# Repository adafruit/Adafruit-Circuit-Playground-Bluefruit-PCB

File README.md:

## Adafruit Adafruit Circuit Playground Bluefruit PCB

<a href="http://www.adafruit.com/products/4333"><br/>
Click here to purchase one from the Adafruit shop</a>

PCB files for the Adafruit Adafruit Circuit Playground Bluefruit. 

Format is EagleCAD schematic and board layout
* https://www.adafruit.com/product/4333

### Description

Circuit Playground Bluefruit is our third board in the Circuit Playground series, another step towards a perfect introduction to electronics and programming. We've taken the popular Circuit Playground Express and made it even better! Now the main chip is an nRF52840 microcontroller which is not only more powerful, but also comes with Bluetooth Low Energy support for wireless connectivity.

The board is round and has alligator-clip pads around it so you don't have to solder or sew to make it work. You can power it from USB, a AAA battery pack, or with a Lipoly battery (for advanced users). Circuit Playground Bluefruit has built-in USB support. Built in USB means you plug it in to program it and it just shows up, no special cable or adapter required. Just program your code into the board then take it on the go!

Here's some of the great goodies baked in to each Circuit Playground Bluefruit:

* 1 x nRF52840 Cortex M4 processor with Bluetooth Low Energy support
* 10 x mini NeoPixels, each one can display any color
* 1 x Motion sensor (LIS3DH triple-axis accelerometer with tap detection, free-fall detection)
* 1 x Temperature sensor (thermistor)
* 1 x Light sensor (phototransistor). Can also act as a color sensor and pulse sensor.
* 1 x Sound sensor (MEMS microphone)
* 1 x Mini speaker with class D amplifier (7.5mm magnetic speaker/buzzer)
* 2 x Push buttons, labeled A and B
* 1 x Slide switch
* 8 x alligator-clip friendly input/output pins
* Includes I2C, UART, 6 pins that can do analog inputs, multiple PWM outputs
* Green "ON" LED so you know its powered
* Red "#13" LED for basic blinking
* Reset button
* 2 MB of SPI Flash storage, used primarily with CircuitPython to store code and libraries.
* MicroUSB port for programming and debugging
* USB port can act like serial port, keyboard, mouse, joystick or MIDI!

### License

Adafruit invests time and resources providing this open source design, please support Adafruit and open-source hardware by purchasing products from [Adafruit](https://www.adafruit.com)!

Designed by Limor Fried/Ladyada for Adafruit Industries.

Creative Commons Attribution/Share-Alike, all text above must be included in any redistribution. 
See license.txt for additional details.

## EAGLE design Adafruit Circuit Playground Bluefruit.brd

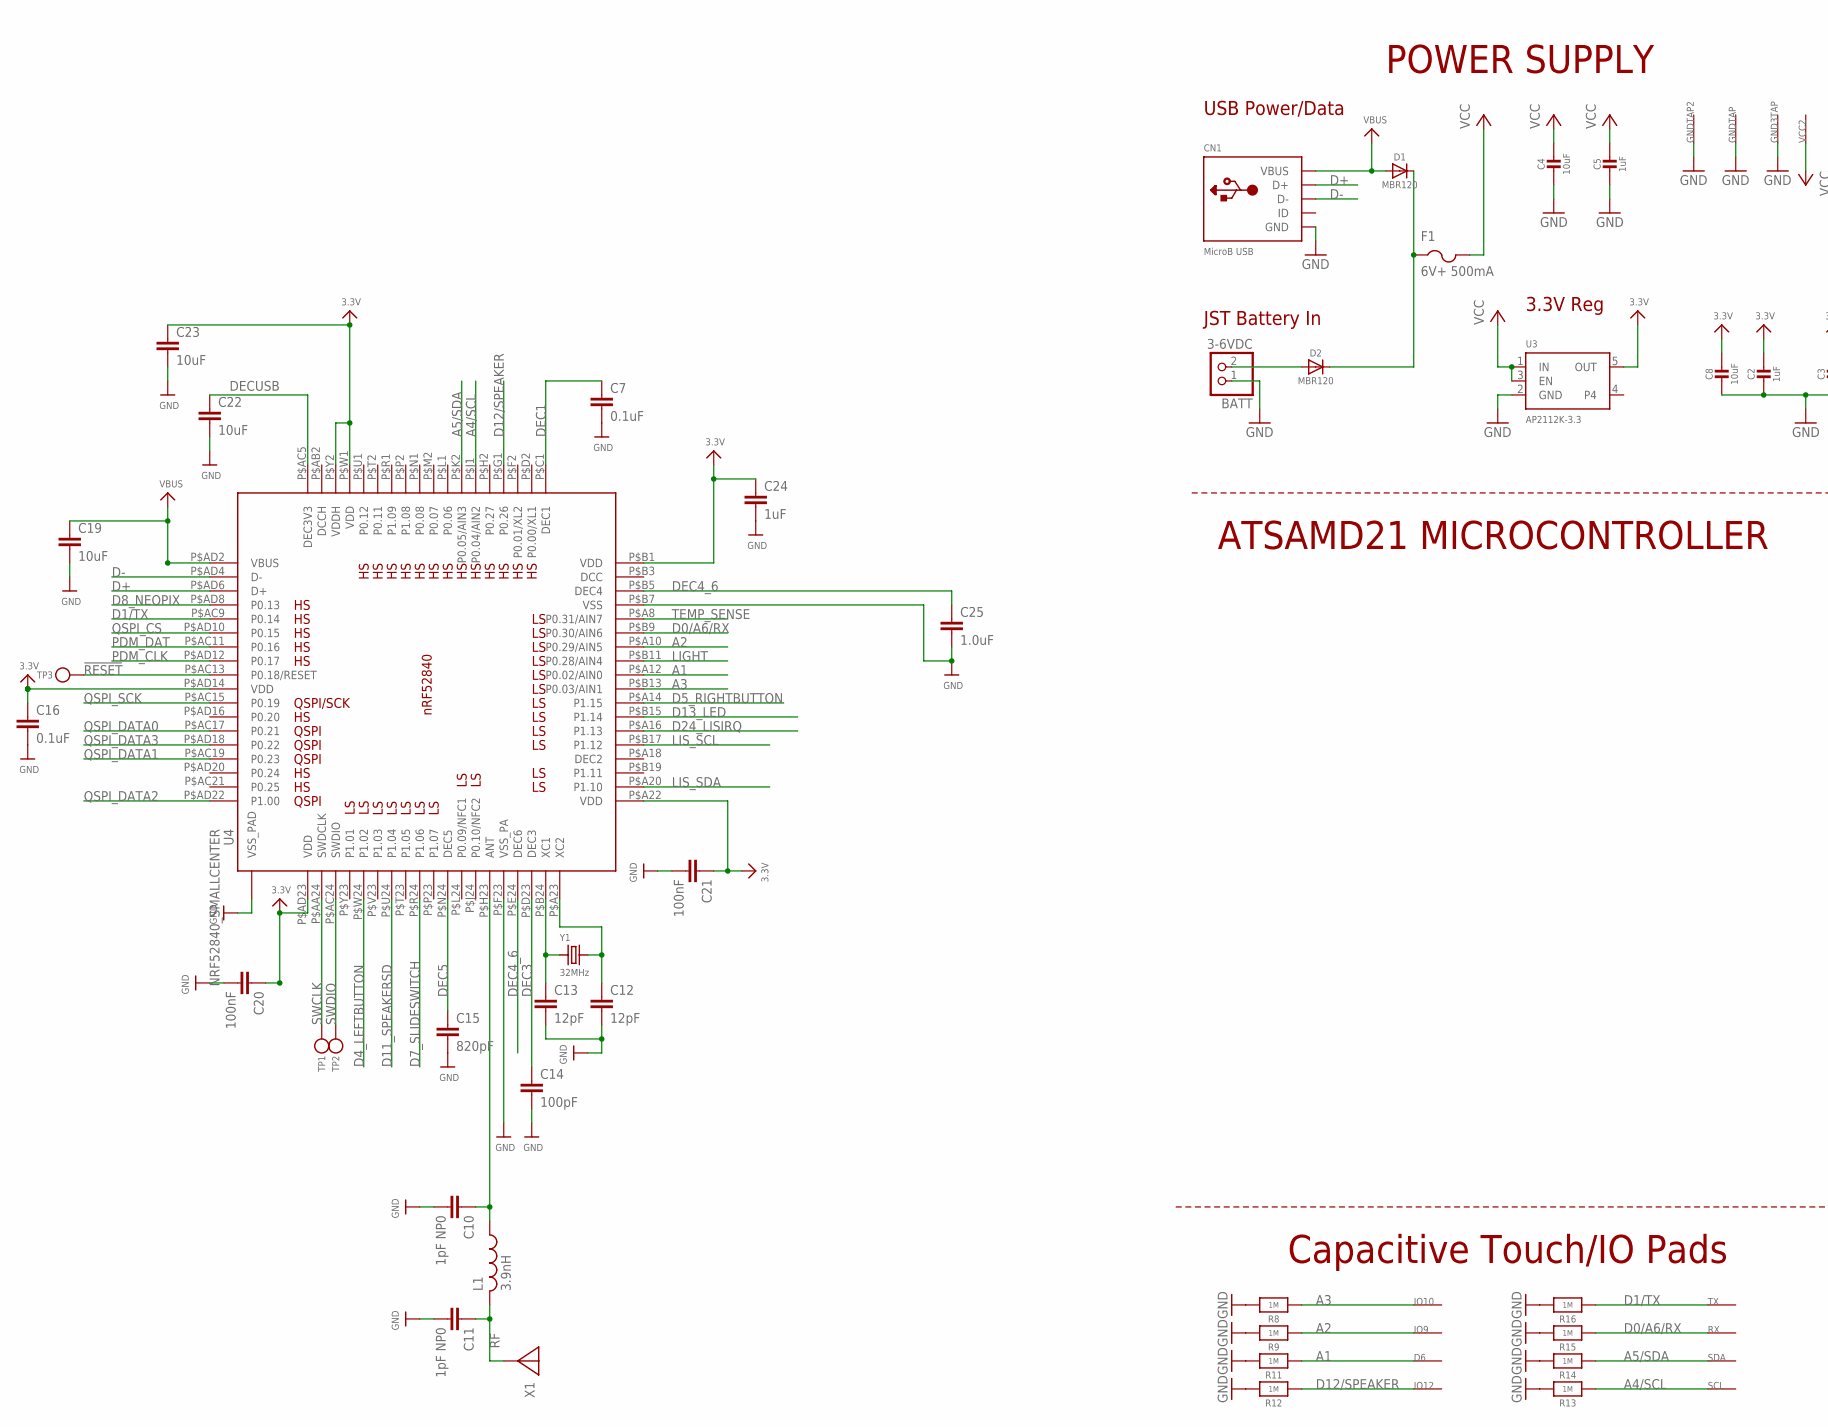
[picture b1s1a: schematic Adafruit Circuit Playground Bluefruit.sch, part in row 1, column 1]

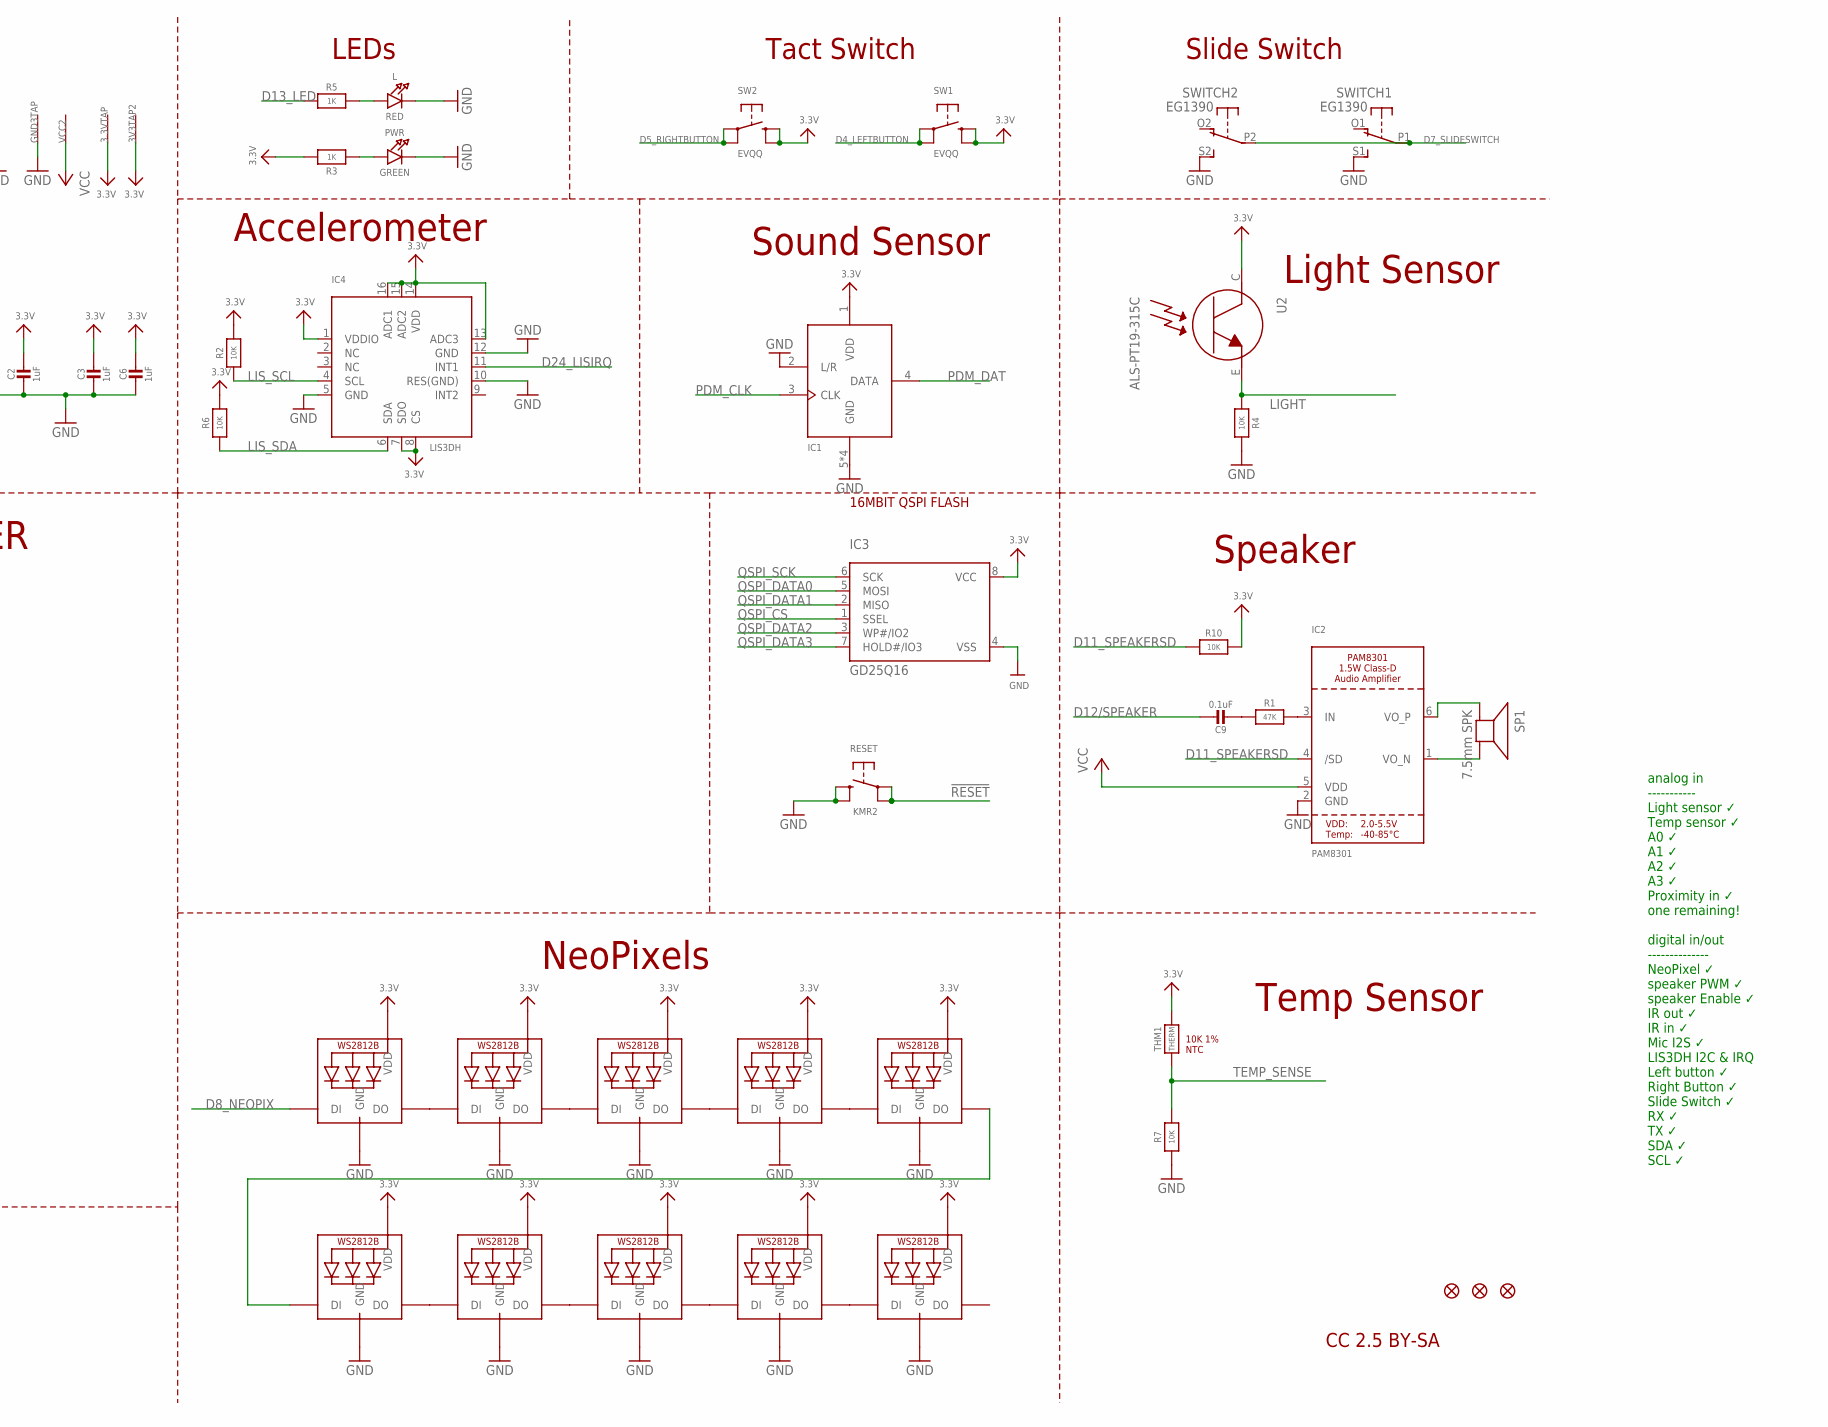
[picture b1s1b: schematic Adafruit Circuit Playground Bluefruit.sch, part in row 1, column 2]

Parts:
3.3VTAP, 3V3TAP2: SEWTAP-ALLIGATOR; SEWALLI
BATT: 3-6VDC; JSTPH2
C2, C3, C5, C6: 1uF; 0603-NO
C4, C8: 10uF; 0805-NO
C7: 0.1uF; RESC0603_N
C9: 0.1uF; 0603-NO
C10, C11: 1pF NP0; RESC0402_N
C12, C13: 12pF; RESC0402_N
C14: 100pF; RESC0402_N
C15: 820pF; RESC0402_N
C16: 0.1uF; RESC0402_N
C19, C22, C23: 10uF; RESC0805_N
C20, C21: 100nF; RESC0402_N
C24: 1uF; RESC0603_N
C25: 1.0uF; RESC0603_N
CN1: MicroB USB; 4UCONN_20329_V2
D1, D2: MBR120; SOD-123
D6: SEWTAP-ALLIGATOR; SEWALLI
F1: 6V+ 500mA; R1206
GND3TAP: SEWTAP-ALLIGATOR; SEWALLI
GNDTAP, GNDTAP2: SEWTAP-ALLIGATOR; SEWALLI
IC1: MIC_PDM; SPK0415HM4H
IC2: PAM8301; SOT23-6
IC3: GD25Q16; USON8
IC4: LIS3DH; LGA16_3X3MM
IO9, IO10, IO12: SEWTAP-ALLIGATOR; SEWALLI
L: RED; CHIPLED_0805_NOOUTLINE
L1: 3.9nH; RESC0402_N
LED1, LED2, LED3, LED4, LED5, LED6, LED7, LED8, LED9, LED10: WS2812B3535; LED3535
PWR: GREEN; CHIPLED_0805_NOOUTLINE
R1: 47K; 0603-NO
R2, R4, R6, R7, R10: 10K; 0603-NO
R3, R5: 1K; 0603-NO
R8, R9, R11, R12, R13, R14, R15, R16: 1M; 0603-NO
RESET: KMR2; BTN_KMR2_4.6X2.8
RX: SEWTAP-ALLIGATOR; SEWALLI
SCL: SEWTAP-ALLIGATOR; SEWALLI
SDA: SEWTAP-ALLIGATOR; SEWALLI
SP1: 7.5mm SPK; BUZZER_SMT_7.5MM
SW1, SW2: EVQQ; EVQ-Q2_SMALLER
SWITCH: EG1390
THM1: THERM; _0402
TP1, TP2, TP3: TESTPOINTROUND1.5MMNO; TESTPOINT_ROUND_1.5MM_NO
TX: SEWTAP-ALLIGATOR; SEWALLI
U2: ALS-PT19-315C
U3: AP2112K-3.3; SOT23-5
U4: NRF52840_SMALLCENTER; AQFN50P700X800X85_HS-74N_SMALLCENTER
U$2, U$3, U$6: FIDUCIAL_1MM
VCC2: SEWTAP-ALLIGATOR; SEWALLI
X1: ANTENNA_JOHANSON_2450AT18B100; ANT_2450AT18B100
Y1: 32MHz; CRYSTAL_2.5X2

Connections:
3.3V: 3.3VTAP.P$1, 3V3TAP2.P$1, C2.1, C3.1, C6.1, C8.1, C16.1, C20.1, C21.1, C23.1, C24.1, IC1.1 (VDD), IC3.8 (VCC), IC4.1 (VDDIO), IC4.7 (SDO), IC4.8 (CS), IC4.13 (ADC3), IC4.14 (VDD), IC4.15 (ADC2), IC4.16 (ADC1), LED1.2 (VDD), LED2.2 (VDD), LED3.2 (VDD), LED4.2 (VDD), LED5.2 (VDD), LED6.2 (VDD), LED7.2 (VDD), LED8.2 (VDD), LED9.2 (VDD), LED10.2 (VDD), R2.2, R3.2, R6.2, R10.2, SW1.B (S), SW1.B' (S1), SW2.B (S), SW2.B' (S1), THM1.2, U2.C, U3.5 (OUT), U4.P$A22 (VDD), U4.P$AD14 (VDD), U4.P$AD23 (VDD), U4.P$B1 (VDD), U4.P$W1 (VDD), U4.P$Y2 (VDDH)
!RESET: RESET.A, RESET.A' (P1), TP3.P$1, U4.P$AC13 (P0.18/RESET)
A1: D6.P$1, R11.1, U4.P$A12 (P0.02/AIN0)
A2: IO9.P$1, R9.1, U4.P$A10 (P0.29/AIN5)
A3: IO10.P$1, R8.1, U4.P$B13 (P0.03/AIN1)
A4/SCL: R13.1, SCL.P$1, U4.P$J1 (P0.04/AIN2)
A5/SDA: R14.1, SDA.P$1, U4.P$K2 (P0.05/AIN3)
D0/A6/RX: R15.1, RX.P$1, U4.P$B9 (P0.30/AIN6)
D1/TX: R16.1, TX.P$1, U4.P$AC9 (P0.14)
D4_LEFTBUTTON: SW1.A, SW1.A' (P1), U4.P$W24 (P1.02)
D5_RIGHTBUTTON: SW2.A, SW2.A' (P1), U4.P$A14 (P1.15)
D7_SLIDESWITCH: SWITCH.P1, SWITCH.P2, U4.P$R24 (P1.06)
D8_NEOPIX: LED6.1 (DI), U4.P$AD8 (P0.13)
D11_SPEAKERSD: IC2.4 (/SD), R10.1, U4.P$U24 (P1.04)
D12/SPEAKER: C9.1, IO12.P$1, R12.1, U4.P$G1 (P0.26)
D13_LED: R5.1, U4.P$B15 (P1.14)
D24_LISIRQ: IC4.11 (INT1), U4.P$A16 (P1.13)
D+: CN1.D+, U4.P$AD6 (D+)
D-: CN1.D-, U4.P$AD4 (D-)
DEC1: C7.1, U4.P$C1 (DEC1)
DEC3: C14.1, U4.P$D23 (DEC3)
DEC4_6: C25.1, U4.P$B5 (DEC4), U4.P$E24 (DEC6)
DEC5: C15.1, U4.P$N24 (DEC5)
DECUSB: C22.1, U4.P$AC5 (DEC3V3)
GND: BATT.1, C2.2, C3.2, C4.2, C5.2, C6.2, C7.2, C8.2, C10.2, C11.2, C12.2, C13.2, C14.2, C15.2, C16.2, C19.2, C20.2, C21.2, C22.2, C23.2, C24.2, C25.2, CN1.BASE@1 (GND), CN1.BASE@2 (GND), CN1.GND, CN1.SPRT@1 (GND), CN1.SPRT@2 (GND), CN1.SPRT@3 (GND), CN1.SPRT@4 (GND), GND3TAP.P$1, GNDTAP.P$1, GNDTAP2.P$1, IC1.2 (L/R), IC1.5 (GND), IC1.6 (GND), IC1.7 (GND), IC1.8 (GND), IC2.2 (GND), IC3.4 (VSS), IC4.5 (GND), IC4.10 (RES(GND)), IC4.12 (GND), L.C, LED1.4 (GND), LED2.4 (GND), LED3.4 (GND), LED4.4 (GND), LED5.4 (GND), LED6.4 (GND), LED7.4 (GND), LED8.4 (GND), LED9.4 (GND), LED10.4 (GND), PWR.C, R4.1, R7.1, R8.2, R9.2, R11.2, R12.2, R13.2, R14.2, R15.2, R16.2, RESET.B (S), RESET.B' (S1), SWITCH.S1 (S), SWITCH.S2 (S), U3.2 (GND), U4.P$B7 (VSS), U4.P$F23 (VSS_PA), U4.THERMPAD (VSS_PAD)
LIGHT: R4.2, U2.E, U4.P$B11 (P0.28/AIN4)
LIS_SCL: IC4.4 (SCL), R2.1, U4.P$B17 (P1.12)
LIS_SDA: IC4.6 (SDA), R6.1, U4.P$A20 (P1.10)
unnamed: PWR.A, R3.1
unnamed: D1.C, D2.C, F1.1
unnamed: C10.1, L1.1, U4.P$H23 (ANT)
unnamed: C9.2, R1.1
unnamed: BATT.2, D2.A
unnamed: IC2.3 (IN), R1.2
unnamed: IC2.6 (VO_P), SP1.+
unnamed: L.A, R5.2
unnamed: LED1.1 (DI), LED2.3 (DO)
unnamed: LED1.3 (DO), LED3.1 (DI)
unnamed: LED2.1 (DI), LED10.3 (DO)
unnamed: LED6.3 (DO), LED7.1 (DI)
unnamed: IC2.1 (VO_N), SP1.-
unnamed: LED7.3 (DO), LED8.1 (DI)
unnamed: LED8.3 (DO), LED9.1 (DI)
unnamed: LED9.3 (DO), LED10.1 (DI)
unnamed: LED3.3 (DO), LED4.1 (DI)
unnamed: LED4.3 (DO), LED5.1 (DI)
unnamed: C12.1, U4.P$A23 (XC2), Y1.3 (2)
unnamed: C13.1, U4.P$B24 (XC1), Y1.1
PDM_CLK: IC1.3 (CLK), U4.P$AD12 (P0.17)
PDM_DAT: IC1.4 (DATA), U4.P$AC11 (P0.16)
QSPI_CS: IC3.1 (SSEL), U4.P$AD10 (P0.15)
QSPI_DATA0: IC3.5 (MOSI), U4.P$AC17 (P0.21)
QSPI_DATA1: IC3.2 (MISO), U4.P$AC19 (P0.23)
QSPI_DATA2: IC3.3 (WP#/IO2), U4.P$AD22 (P1.00)
QSPI_DATA3: IC3.7 (HOLD#/IO3), U4.P$AD18 (P0.22)
QSPI_SCK: IC3.6 (SCK), U4.P$AC15 (P0.19)
RF: C11.1, L1.2, X1.FP
SWCLK: TP1.P$1, U4.P$AA24 (SWDCLK)
SWDIO: TP2.P$1, U4.P$AC24 (SWDIO)
TEMP_SENSE: R7.2, THM1.1, U4.P$A8 (P0.31/AIN7)
VBUS: C19.1, CN1.VBUS, D1.A, U4.P$AD2 (VBUS)
VCC: C4.1, C5.1, F1.2, IC2.5 (VDD), U3.1 (IN), U3.3 (EN), VCC2.P$1

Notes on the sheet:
CC 2.5 BY-SA
10K 1% NTC
ATSAMD21 MICROCONTROLLER
USB Power/Data
JST Battery In
3.3V Reg
POWER SUPPLY
NeoPixels
Speaker
Temp Sensor
Light Sensor
Sound Sensor
Slide Switch
Tact Switch
LEDs
Accelerometer
Capacitive Touch/IO Pads
analog in ----------- Light sensor ✓ Temp sensor ✓ A0 ✓ A1 ✓ A2 ✓ A3 ✓ Proximity in ✓ one remaining! digital in/out -------------- NeoPixel ✓ speaker PWM ✓ speaker Enable ✓ IR out ✓ IR in ✓ Mic I2S ✓ LIS3DH I2C & IRQ Left button ✓ Right Button ✓ Slide Switch ✓ RX ✓ TX ✓ SDA ✓ SCL ✓
16MBIT QSPI FLASH

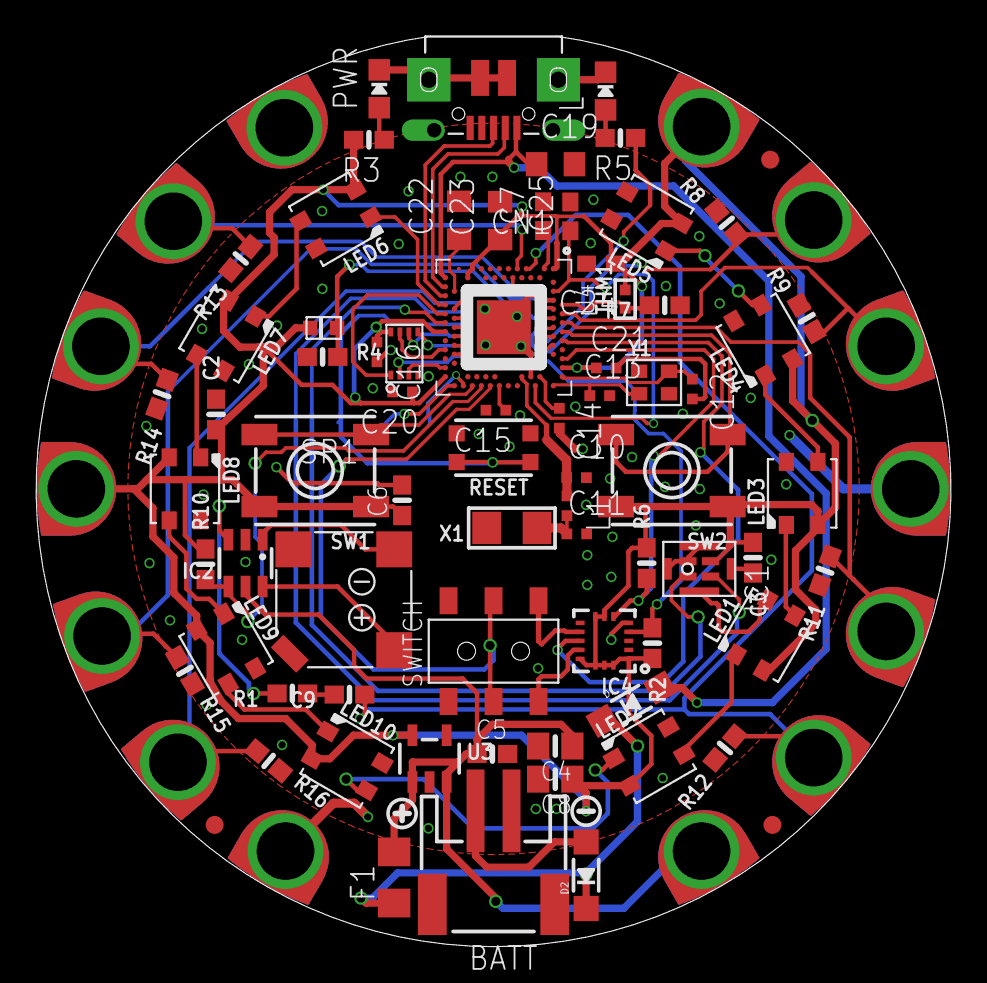
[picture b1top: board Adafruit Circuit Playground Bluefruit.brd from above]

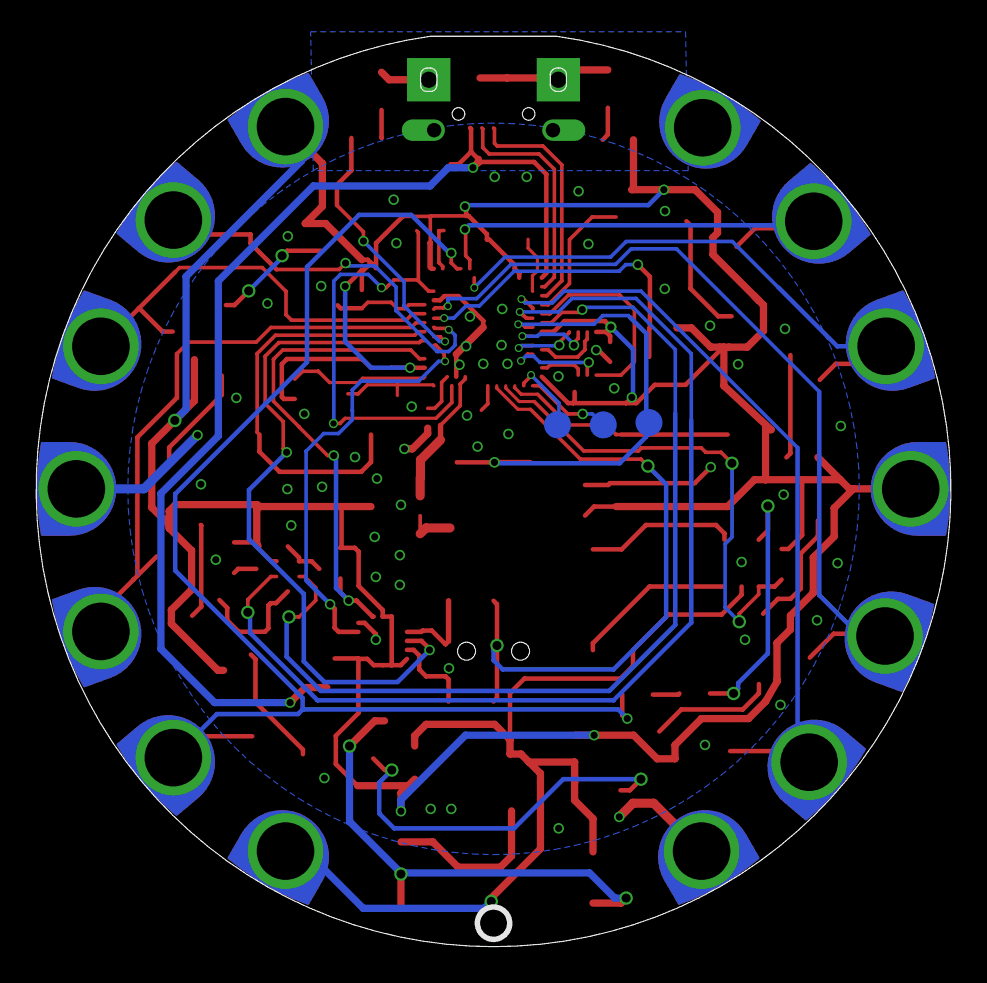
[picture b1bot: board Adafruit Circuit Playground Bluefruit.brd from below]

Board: 4 copper layers, 50.8 x 50.6 mm, 96 parts (5 on the bottom side), 62 nets.

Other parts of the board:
U$1: SYMBOL_MINUS
U$7: PCBFEAT-REV-040
U$16: CPLAY_BLUEFRUIT_BOT
U$35: SYMBOL_PLUS
U$44: CPLAY_BLUEFRUIT_TOP

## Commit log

2019-09-05 Adding PCB files.
2020-03-02 Deleting previous rev.
2020-03-02 Upload new board files.
2021-05-15 Add pin reference PDF

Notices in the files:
parts and their libraries:
microbuilder: This work is placed in the public domain, and may be freely used for commercial and non-commercial work with the following conditions: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
